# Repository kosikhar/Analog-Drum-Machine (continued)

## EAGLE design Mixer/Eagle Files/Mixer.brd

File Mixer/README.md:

Design Information for Analog Drum Machine Mixer Circuit

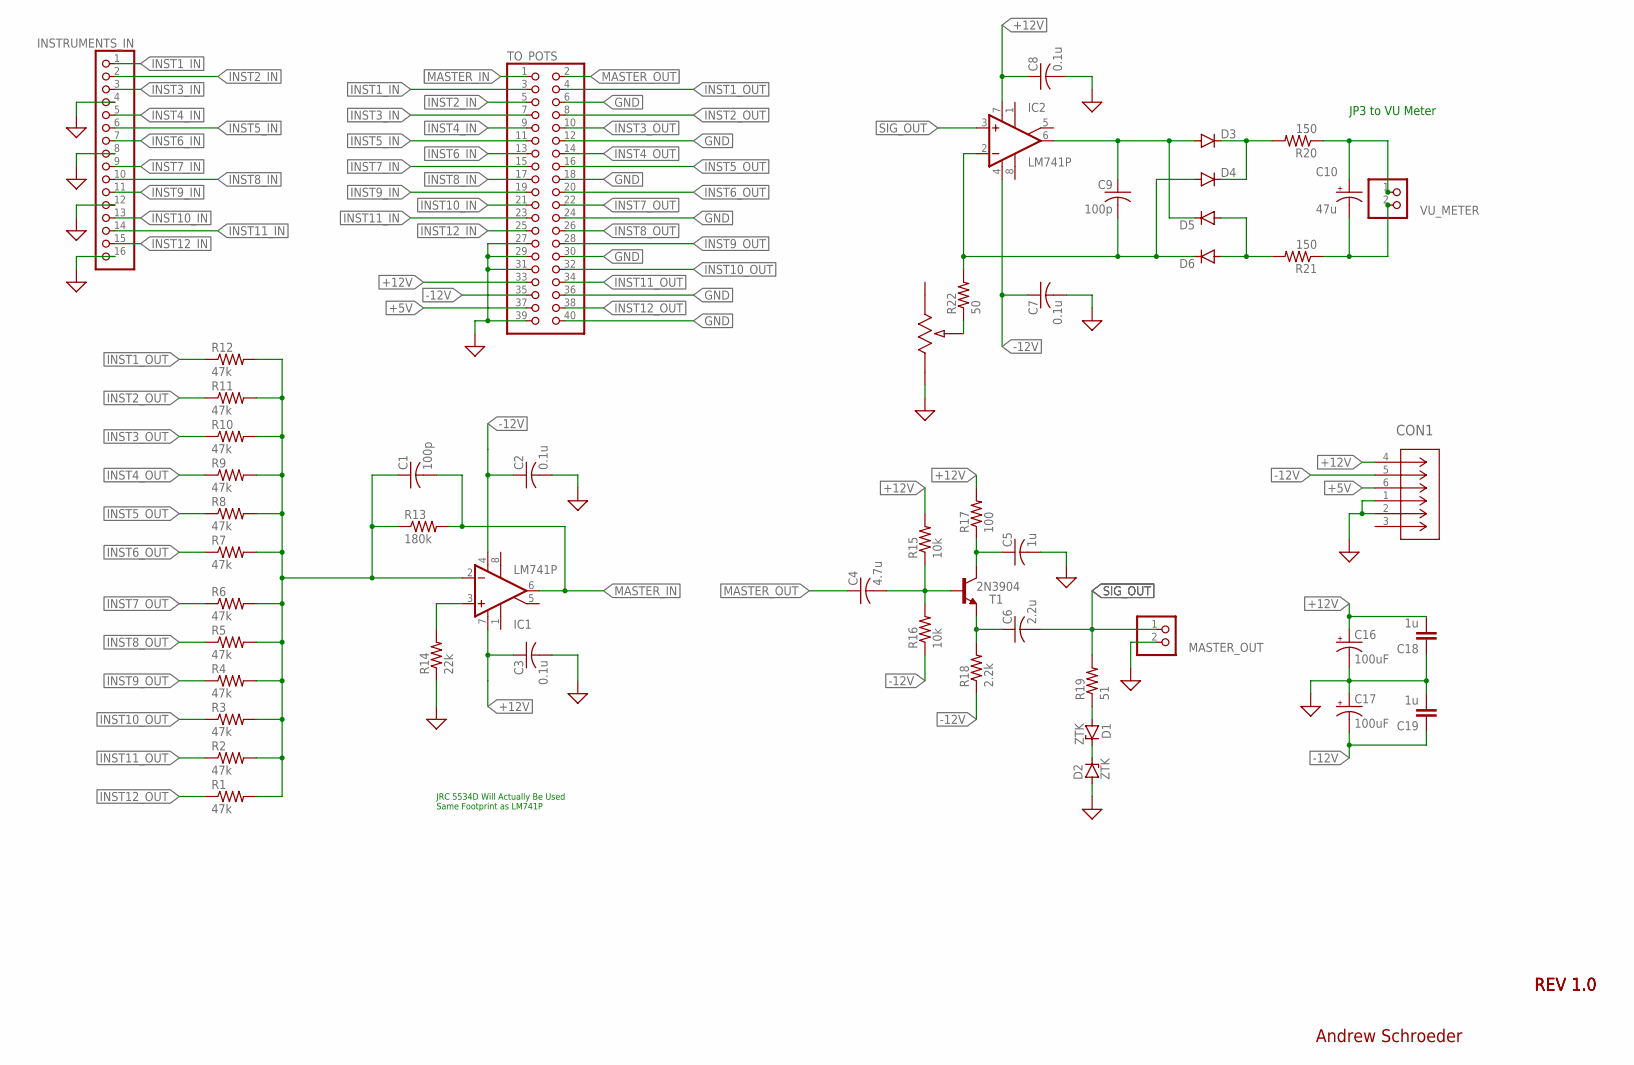
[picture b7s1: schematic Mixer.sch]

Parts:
C1, C9: 100p; C025-025X050
C2, C3, C7, C8: 0.1u; C025-025X050
C4: 4.7u; C025-025X050
C5: 1u; C025-025X050
C6: 2.2u; C025-025X050
C10: 47u; E2-5
C16, C17: 100uF; E5-8,5
C18, C19: 1u; C050-024X044
CON1: 1-770875-01-770875-0_VERTICAL; 1-770875-0
D1, D2: ZTK; DO35Z10
D3, D4, D5, D6: 1N4148DO35-7; DO35-7
IC1, IC2: LM741P; DIL08
INSTRUMENTS_IN: PINHD-1X16; 1X16
MASTER_OUT: PINHD-1X2; 1X02
R1, R2, R3, R4, R5, R6, R7, R8, R9, R10, R11, R12: 47k; 0207/7
R13: 180k; 0207/7
R14: 22k; 0207/7
R15, R16: 10k; 0207/7
R17: 100; 0207/7
R18: 2.2k; 0207/7
R19: 51; 0207/7
R20, R21: 150; 0207/7
R22: 50; 0207/7
R23: PV36W101C01B00; POT_PV36W
T1: 2N3904; TO92
TO_POTS: PINHD-2X20; 2X20
VU_METER: PINHD-1X2; 1X02

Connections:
+5V: CON1.6 (3), TO_POTS.37
+12V: C3.1, C8.1, C16.+, C18.2, CON1.4 (1), IC1.7 (V+), IC2.7 (V+), R15.2, R17.2, TO_POTS.33
-12V: C2.1, C7.1, C17.-, C19.1, CON1.5 (2), IC1.4 (V-), IC2.4 (V-), R16.1, R18.1, TO_POTS.35
GND: C2.2, C3.2, C5.2, C7.2, C8.2, C16.-, C17.+, C18.1, C19.2, CON1.1 (4), CON1.2 (5), D2.A, INSTRUMENTS_IN.4, INSTRUMENTS_IN.8, INSTRUMENTS_IN.12, INSTRUMENTS_IN.16, MASTER_OUT.2, R14.1, R23.3, TO_POTS.6, TO_POTS.12, TO_POTS.18, TO_POTS.24, TO_POTS.27, TO_POTS.29, TO_POTS.30, TO_POTS.31, TO_POTS.36, TO_POTS.39, TO_POTS.40
INST1_IN: INSTRUMENTS_IN.1, TO_POTS.3
INST1_OUT: R12.1, TO_POTS.4
INST2_IN: INSTRUMENTS_IN.2, TO_POTS.5
INST2_OUT: R11.1, TO_POTS.8
INST3_IN: INSTRUMENTS_IN.3, TO_POTS.7
INST3_OUT: R10.1, TO_POTS.10
INST4_IN: INSTRUMENTS_IN.5, TO_POTS.9
INST4_OUT: R9.1, TO_POTS.14
INST5_IN: INSTRUMENTS_IN.6, TO_POTS.11
INST5_OUT: R8.1, TO_POTS.16
INST6_IN: INSTRUMENTS_IN.7, TO_POTS.13
INST6_OUT: R7.1, TO_POTS.20
INST7_IN: INSTRUMENTS_IN.9, TO_POTS.15
INST7_OUT: R6.1, TO_POTS.22
INST8_IN: INSTRUMENTS_IN.10, TO_POTS.17
INST8_OUT: R5.1, TO_POTS.26
INST9_IN: INSTRUMENTS_IN.11, TO_POTS.19
INST9_OUT: R4.1, TO_POTS.28
INST10_IN: INSTRUMENTS_IN.13, TO_POTS.21
INST10_OUT: R3.1, TO_POTS.32
INST11_IN: INSTRUMENTS_IN.14, TO_POTS.23
INST11_OUT: R2.1, TO_POTS.34
INST12_IN: INSTRUMENTS_IN.15, TO_POTS.25
INST12_OUT: R1.1, TO_POTS.38
MASTER_IN: C1.2, IC1.6 (OUT), R13.2, TO_POTS.1
MASTER_OUT: C4.1, TO_POTS.2
unnamed: C9.1, D3.A, D5.C, IC2.6 (OUT)
unnamed: IC1.3 (+IN), R14.2
unnamed: C9.2, D4.A, D6.C, IC2.2 (-IN), R22.2
unnamed: C1.1, IC1.2 (-IN), R1.2, R2.2, R3.2, R4.2, R5.2, R6.2, R7.2, R8.2, R9.2, R10.2, R11.2, R12.2, R13.1
unnamed: D5.A, D6.A, R21.2
unnamed: C4.2, R15.1, R16.2, T1.2 (B)
unnamed: C10.+, R20.1, VU_METER.1
unnamed: C5.1, R17.1, T1.1 (C)
unnamed: D3.C, D4.C, R20.2
unnamed: C6.1, R18.2, T1.3 (E)
unnamed: C10.-, R21.1, VU_METER.2
unnamed: D1.A, R19.1
unnamed: R22.1, R23.2
unnamed: D1.C, D2.C
SIG_OUT: C6.2, IC2.3 (+IN), MASTER_OUT.1, R19.2

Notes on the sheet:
JRC 5534D Will Actually Be Used Same Footprint as LM741P
JP3 to VU Meter
REV 1.0
Andrew Schroeder

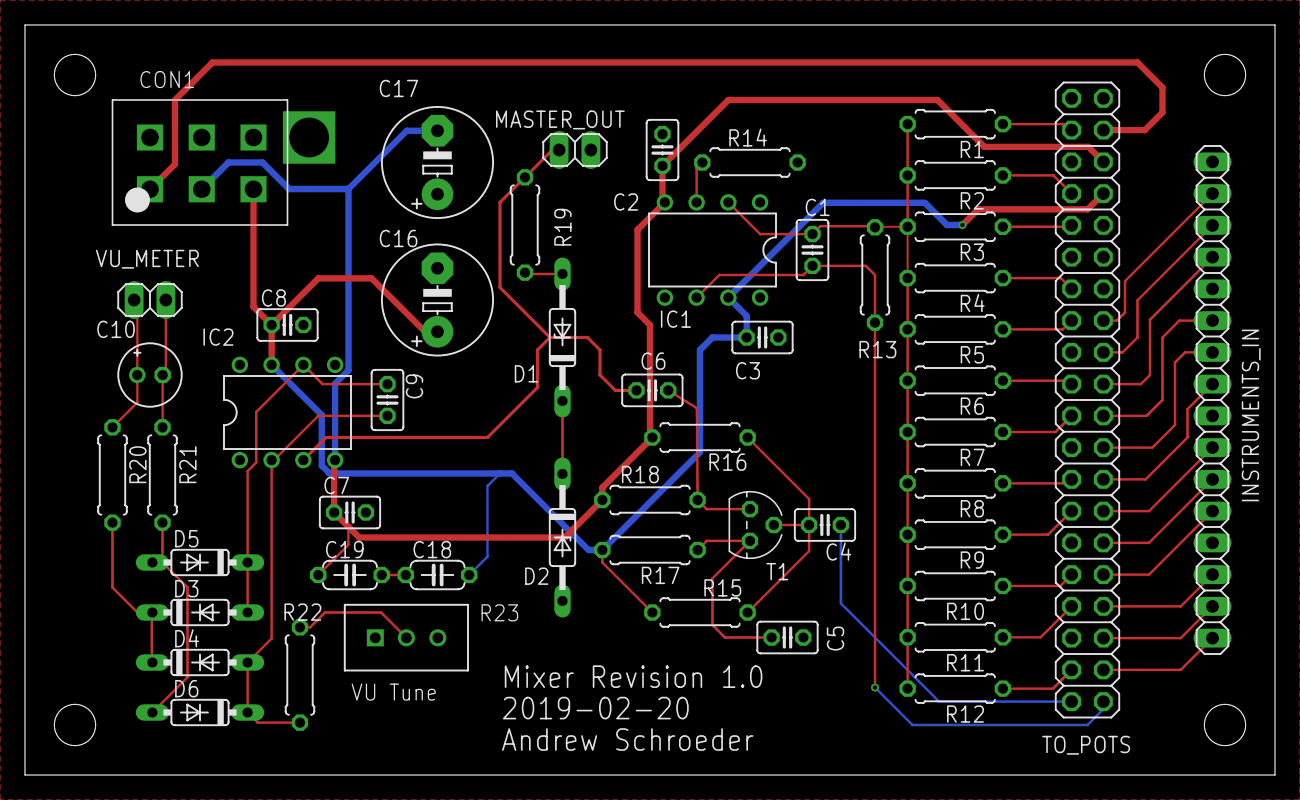
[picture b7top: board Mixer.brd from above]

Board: 2 copper layers, 100.0 x 60.0 mm, 56 parts (0 on the bottom side), 45 nets.

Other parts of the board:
U$1, U$2, U$3, U$4: STAND-OFF
U$5: A5L-LOC

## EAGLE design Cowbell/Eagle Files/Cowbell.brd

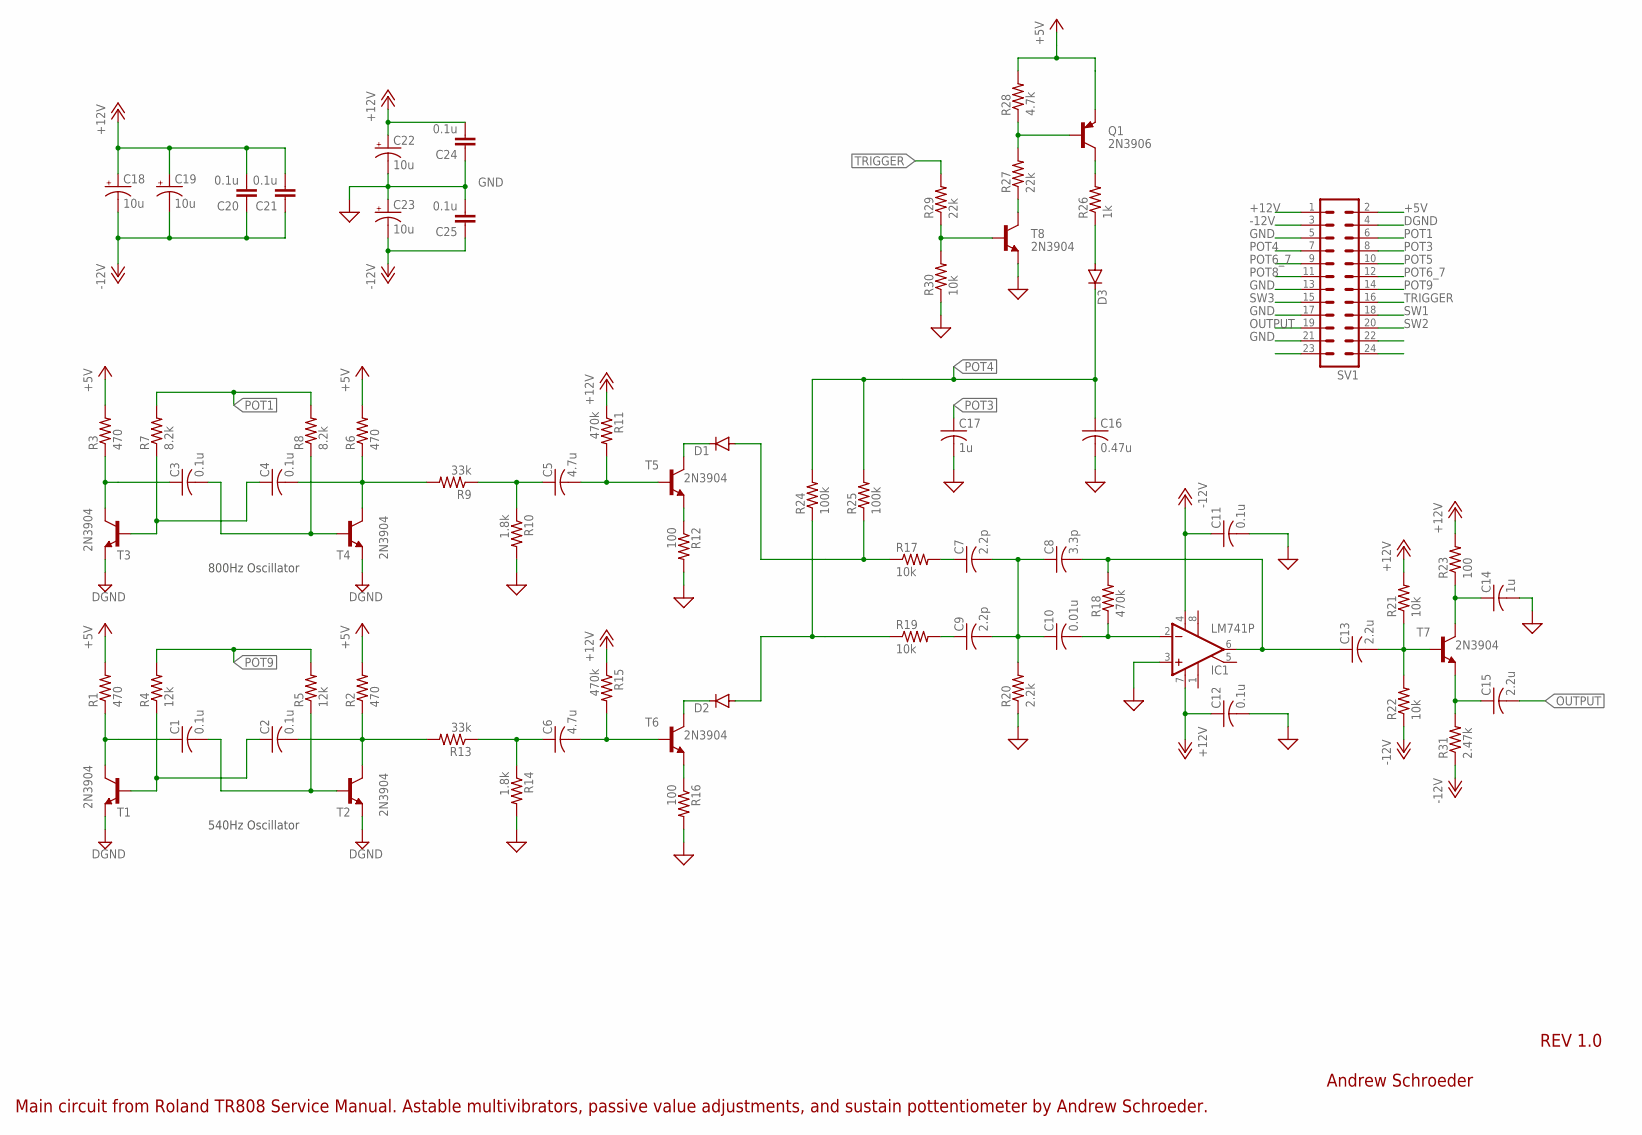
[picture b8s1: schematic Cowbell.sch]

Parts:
C1, C2, C3, C4, C11, C12: 0.1u; C025-024X044
C5, C6: 4.7u; C025-024X044
C7, C9: 2.2p; C025-024X044
C8: 3.3p; C025-024X044
C10: 0.01u; C025-024X044
C13, C15: 2.2u; C025-024X044
C14, C17: 1u; C025-024X044
C16: 0.47u; C025-024X044
C18, C19, C22, C23: 10u; E2,5-6
C20, C21, C24, C25: 0.1u; C050-024X044
D1, D2, D3: 1N4148DO35-7; DO35-7
IC1: LM741P; DIL08
Q1: 2N3906; TO92
R1, R2, R3, R6: 470; 0207/7
R4, R5: 12k; 0207/7
R7, R8: 8.2k; 0207/7
R9, R13: 33k; 0207/7
R10, R14: 1.8k; 0207/7
R11, R15, R18: 470k; 0207/7
R12, R16, R23: 100; 0207/7
R17, R19, R21, R22, R30: 10k; 0207/7
R20: 2.2k; 0207/7
R24, R25: 100k; 0207/7
R26: 1k; 0207/7
R27, R29: 22k; 0207/7
R28: 4.7k; 0207/7
R31: 2.47k; 0207/7
SV1: MA12-2
T1, T2, T3, T4, T5, T6, T7, T8: 2N3904; TO92

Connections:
+5V: Q1.3 (E), R1.2, R2.2, R3.2, R6.2, R28.2, SV1.2
+12V: C12.1, C18.+, C19.+, C20.2, C21.2, C22.+, C24.2, IC1.7 (V+), R11.1, R15.1, R21.2, R23.2, SV1.1
-12V: C11.1, C18.-, C19.-, C20.1, C21.1, C23.-, C25.1, IC1.4 (V-), R22.1, R31.1, SV1.3
DGND: SV1.4, T1.3 (E), T2.3 (E), T3.3 (E), T4.3 (E)
GND: C11.2, C12.2, C14.2, C16.2, C17.2, C22.-, C23.+, C24.1, C25.2, IC1.3 (+IN), R10.2, R12.2, R14.2, R16.2, R20.1, R30.1, SV1.5, SV1.13, SV1.17, SV1.21, T8.3 (E)
unnamed: C4.2, R6.1, R9.2, T4.1 (C)
unnamed: C2.2, R2.1, R13.2, T2.1 (C)
unnamed: C1.1, R1.1, T1.1 (C)
unnamed: C2.1, R4.1, T1.2 (B)
unnamed: C3.1, R3.1, T3.1 (C)
unnamed: C4.1, R7.1, T3.2 (B)
unnamed: C1.2, R5.1, T2.2 (B)
unnamed: C3.2, R8.1, T4.2 (B)
unnamed: C5.1, R9.1, R10.1
unnamed: D1.C, T5.1 (C)
unnamed: C5.2, R11.2, T5.2 (B)
unnamed: R12.1, T5.3 (E)
unnamed: C6.1, R13.1, R14.1
unnamed: C6.2, R15.2, T6.2 (B)
unnamed: R16.1, T6.3 (E)
unnamed: D2.C, T6.1 (C)
unnamed: D1.A, R17.1, R25.1
unnamed: D2.A, R19.1, R24.1
unnamed: C7.1, R17.2
unnamed: C7.2, C8.1, C9.2, C10.1, R20.2
unnamed: C8.2, C13.1, IC1.6 (OUT), R18.2
unnamed: C10.2, IC1.2 (-IN), R18.1
unnamed: C13.2, R21.1, R22.2, T7.2 (B)
unnamed: C9.1, R19.2
unnamed: Q1.1 (C), R26.2
unnamed: C14.1, R23.1, T7.1 (C)
unnamed: C15.1, R31.2, T7.3 (E)
unnamed: R27.1, T8.1 (C)
unnamed: D3.A, R26.1
unnamed: R29.1, R30.2, T8.2 (B)
unnamed: Q1.2 (B), R27.2, R28.1
OUTPUT: C15.2, SV1.19
POT1: R7.2, R8.2, SV1.6
POT3: C17.1, SV1.8
POT4: C16.1, D3.C, R24.2, R25.2, SV1.7
POT5: SV1.10
POT6_7: SV1.9, SV1.12
POT8: SV1.11
POT9: R4.2, R5.2, SV1.14
SW1: SV1.18
SW2: SV1.20
SW3: SV1.15
TRIGGER: R29.2, SV1.16

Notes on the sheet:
540Hz Oscillator
800Hz Oscillator
Andrew Schroeder
REV 1.0
Main circuit from Roland TR808 Service Manual. Astable multivibrators, passive value adjustments, and sustain pottentiometer by Andrew Schroeder.

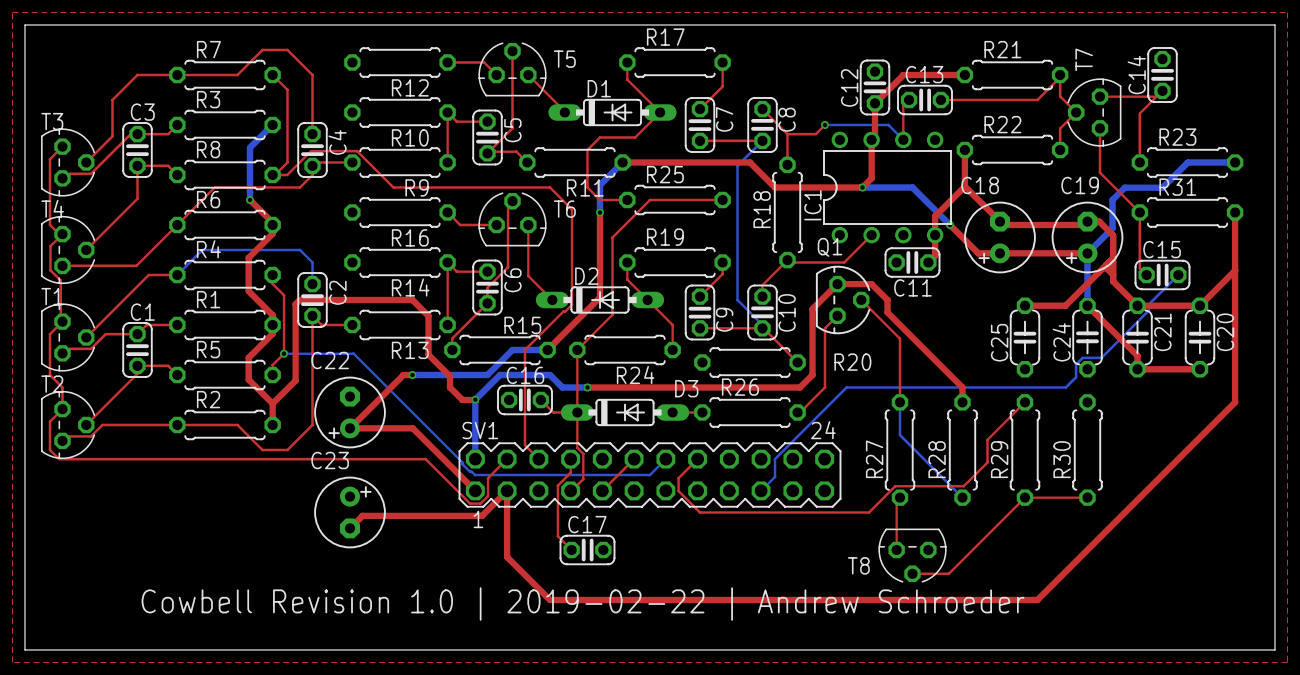
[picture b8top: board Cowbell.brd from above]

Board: 2 copper layers, 100.0 x 50.0 mm, 71 parts (0 on the bottom side), 43 nets.

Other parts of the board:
U$6: A5L-LOC

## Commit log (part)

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2018-10-19 Added kick drum and updated gitignore
2018-10-20 preliminary
2018-11-07 Create Main board
2018-11-07 removed empty file
2018-11-07 First push
    Initial upload.
2018-11-07 Schematic
    Only schematic added
2018-11-11 some changes to the kick
2018-11-12 Created new branch and README.md for Mixer
2018-11-12 Created Input Module Simulation-Still Under Testing
2018-11-12 Added Mixer Input Module
2018-11-13 Added power supply V2
2018-11-13 Added Summing Circuit
2018-11-13 Deleted Temporary Files
2018-11-14 Added Hi Hat simulation
2018-11-14 Added Amplifier Stage and Selected Caps for Cutoff Frequency=40kHz
2018-11-14 CIrcuit for switches
    Seperate schematic for switches (Updated)
2018-11-14 Cleaned up schematics
    Instruments, switches and initial diagram.
2018-11-14 Updated schematics
    Removed #s files
2018-11-16 Added BOM
2018-11-16 missed some parts for the BOM
2018-11-18 Kick drum (#1)
    * some changes to the kick
    * Added BOM
    * missed some parts for the BOM
2018-11-19 Initial circuits
    Similations seem okay.
2018-11-20 Added Subcircuit model for LM741
2018-11-20 Added Cowbell Simulation Files
2018-11-22 changes to envolope
2018-11-22 changes to feedback/osc
2018-11-25 This is pretty much close to the final form
    Not much needed to change here. Kick sounds great
2018-11-25 changes to some names and added sounds
2018-11-25 added block diagram
2018-11-26 Created Enclosure Branch and uploaded models for backup
2018-11-26 added monochrome pdf print out
2018-11-26 Changed block diagram
2018-11-26 Sequencer State Diagrams update
2018-11-26 Work on state diagram
2018-11-26 update State diagram
2018-11-26 updated state diagram
2018-11-26 Added to State Diagram
2018-11-26 Updated sequencer diagram
2018-11-26 finishing touches
2018-11-26 K I think this is done
2018-11-26 k this should be good now
2018-11-26 Committing to switch branches
2018-11-26 changed name of BOM
2018-11-26 Added BOM list
2018-11-27 Updated Power Supply Branch
    Updated Power supply branch with newest LTspice models, as well as Eagle Schematic and block diagram. BOM updated as well.
2018-11-27 Updated Hi Hat
    Updated Hi Hat simulation and added BOM and block diagram
2018-11-29 Updated LTspice and wave files
    Added the LTspice simulation that uses the white noise wave file. Uploaded new sounds
2018-12-08 Added version with diff amp
2018-12-09 Added the Schmitt Triggers
2018-12-09 moved blocks over
2018-12-09 revert
2018-12-09 initialize
2018-12-10 added full diagram
2018-12-18 intialized more files
2018-12-19 Added more intializers
2018-12-20 Added a dedicated timer class, worked on shiftregister class
2018-12-21 Got the timer interrupt working.
2018-12-21 work on timers/interrupt/SIPO
2018-12-22 This doesn't work. Need to fix
2018-12-24 okay it seems I got stuff to work now
2018-12-24 can sucessfully write to a seven segment
2018-12-25 code tested with a second SIPO shift register
2018-12-25 Made timer faster. Small cleanup
2018-12-26 Code cleanup and optimization
    - Added in a primitive task mangement system
    - Optimized the speed of shifts.
2019-01-14 added 1ms pulse source
2019-01-20 Organized folder structure.
2019-01-21 Made changes to power supply PCB
2019-01-24 started eagle schematic
2019-01-24 work on schematic
2019-01-26 Power supply PCB still in progress
2019-01-26 perf board for instruments plus gerbers
2019-01-26 perf board for instruments plus gerbers (#2)
2019-01-26 Finished PCB
2019-01-27 Pretty much done schematic
2019-01-28 Just Viewed
2019-01-28 Updated Mixer
2019-01-28 Just switching branches
2019-01-28 Switching Branches Again
2019-01-28 Revised Mixer
2019-01-28 Added Mixer_BOM
2019-01-28 updated BOM
2019-01-28 Power supply (#3)
    * preliminary
    * Added power supply V2
    * Update Power Supply/Thumbs.db
    * Updated Power Supply Branch
    Updated Power supply branch with newest LTspice models, as well as Eagle Schematic and block diagram. BOM updated as well.
    * Added version with diff amp
2019-01-28 Switching Branches
2019-01-29 work on pcb.
    -laying out components
2019-01-30 Wiring PCB
    -Almost done!
2019-01-30 Updated some capacitors
    Changed some caps from 2.2uF to 4.7uF, got rid of a 4.7uF
2019-01-30 Added Revised Order Form
2019-01-31 I think im done
2019-01-31 Analog Drum (#4)
    * some changes to the kick
    * Added BOM
    * missed some parts for the BOM
    * changes to envolope
    * changes to feedback/osc
    * This is pretty much close to the final form
2019-01-31 Made Updates
    Made Updates
2019-02-03 Create VU meter schematic.sch
    VU meter initial commit
2019-02-03 Update VU meter schematic.sch
    Fixed some routing issues.
2019-02-03 PCB files
    Updated with PCB files
2019-02-04 Major overhaul of task managment.
    - Not tested yet, but it compiles
2019-02-04 small changes
2019-02-04 u don ducked
2019-02-05 New backend complete and works
    -Should be easier to read and find out what things do
    -Should be easier to add new functionality
2019-02-05 Added folders clean up mess of files
2019-02-07 This probs dont work
2019-02-08 Added shift register piso
2019-02-08 not complete
    -working on removing bugs
2019-02-08 fixed bug.
2019-02-09 Added some class definitions
2019-02-09 added some headers to project
2019-02-10 added some declarations
2019-02-12 Minor modifications
2019-02-15 Create Main board.sch
    Version 1
2019-02-17 Removed op-amp buffer stage from mixer circuit.
2019-02-17 Nothing important
2019-02-18 Added circuitry for testing frequency response.
2019-02-18 Cleaned up useless files.
2019-02-20 Built preliminary Mixer Schematic
2019-02-20 Update Main board.sch
    Updated pinouts. Need feedback.
2019-02-21 Created Board File
2019-02-21 Completed Mixer Board Layout
2019-02-21 Organized files and folders.
2019-02-21 Added to input polling task
2019-02-21 Create Main board.brd
    Initial version. Could definitely be improved.
2019-02-21 Update Main board.sch
    Updated version with wiring.
2019-02-21 Update Main board.brd
    Version 2
2019-02-22 Updated LTspice file with values used during prototype on breadboard.
2019-02-22 Addeed design references folder.
2019-02-22 Touched up schematic and started board layout.
2019-02-22 Placed parts on .brd file. Have to route yet.
2019-02-22 Repositioned main header.
2019-02-22 Completed board layout, generated CAM files, and organized files and folders.
2019-02-22 Ran DRC and fixed errors. Generated CAM files and updated images.
2019-02-22 button input
2019-02-22 Added note to clarify analog and digital ground
    Added note to clarify analog and digital ground. Pin 3 is digital, 1 & 2 are analog.
2019-02-22 Made some small changes for design review. More yet to be made.
2019-02-23 Got analog input to work
2019-02-23 Updated Solidworks model with accurate dimensions.
2019-02-23 Made the trigger fall in line with BPM
2019-02-24 Made BPM display update faster
2019-02-25 Started Snare PCB
2019-03-03 updated input code
2019-03-03 exported library
2019-03-03 Edited TE6Pin
2019-03-03 Updated TE part
2019-03-03 Added 6Pin TE vertical
2019-03-03 ignoring local backups
2019-03-03 Main board
    Relabelled everything with power supply, labelled and redid traces.
2019-03-03 Finished Schematic
    Finished Schematic
2019-03-04 Updated Snare schematic
    updated snare schematic
2019-03-04 Started PCB
    Started working on the PCB
2019-03-04 First draft of schematic
2019-03-04 Finished PCB
    Finished the snare PCB
2019-03-04 Implemented changes from design review meeting.
2019-03-04 fixed TE pinout
2019-03-05 Sequencer microcontroller (#7)
    * Sequencer State Diagrams update
    * Work on state diagram
    * update State diagram
    * updated state diagram
    * Added to State Diagram
    * Updated sequencer diagram
2019-03-05 Version 2 of mainboard
    Corrected lots of thingamajics.
2019-03-05 Finished Silkscreen
2019-03-05 Added a few missing components
    Added a few missing components. 3 coupling capacitors were missing
2019-03-05 Generated Gerbers
2019-03-05 Created Gerbers again and fixed Seeed DRC errors
    Created Gerbers again and fixed Seeed DRC errors
2019-03-05 Created to interface panel.
2019-03-05 Finished layout - needs silk screen
2019-03-05 some track adjustments
2019-03-05 Version 3 of mainboard
    Added sequencer pinouts and manually did all traces.
2019-03-05 Version 4
    Added ground traces to previous version.
2019-03-05 This board should work
2019-03-05 Swapped Instruments 2 and 3
    Swapped instruments 2 and 3 so they are in proper order
2019-03-06 Added silk screen
2019-03-06 PATA breakout
2019-03-06 did DRC
2019-03-06 Just added some SR
2019-03-06 Added 100ohm resistor
2019-03-06 updated gitignore
2019-03-06 Attached traces to resistor and created gerbers
2019-03-06 Fixed air wires and created gerbers
2019-03-06 some board layout
2019-03-07 breakout backside
2019-03-07 Finished routing
2019-03-07 Finished top board - ran DRC
2019-03-07 Pata breakout sequencer (#10)
    * Just added some SR
    * Update .gitignore
    * Delete Analog Drum_2019-01-31.zip
    * updated gitignore
    * some board layout
    * split board into 2
2019-03-07 Main board (#8)
    * First push
    Initial upload.
    * Schematic
    Only schematic added
    * Delete Main board schematic.zip
    * CIrcuit for switches
2019-03-07 Pata breakout (#9)
    * PATA breakout
    * did DRC
    * Delete .PATA Breakout.sch.lck
2019-03-07 Cowbell (#6)
    * preliminary
    * Added power supply V2
    * Update Power Supply/Thumbs.db
    * Added Cowbell Simulation Files
    * Committing to switch branches
    * Added the Schmitt Triggers
2019-03-07 Mixer (#5)
    * Created new branch and README.md for Mixer
    * Created Input Module Simulation-Still Under Testing
    * Added Mixer Input Module
    * Added Summing Circuit
    * Deleted Temporary Files
    * Added Amplifier Stage and Selected Caps for Cutoff Frequency=40kHz
2019-03-07 cleanup
2019-03-07 Snare (#11)
    * Started Snare PCB
    * Finished Schematic
    Finished Schematic
    * Updated Snare schematic
    updated snare schematic
    * Started PCB
2019-03-07 Changed hole sizes for rotary encoders on measure select and bpm controls.
2019-03-07 Created DWG and DXF files for the top panel for machine shop.
2019-03-07 Updated top panel pdf with new dimensions.
2019-03-11 Started Hi-Hat PCB
    Started Hi-Hat PCB
2019-03-11 Completed most of hi-hat schematic
2019-03-11 added rotary switch classs
2019-03-12 Changed resistors out for shorter ones
    changed resistors out for shorter ones
2019-03-13 Made a few adjustments on top panel, made back panel.
2019-03-13 Updated back panel drawing.
2019-03-14 Added piano hinge holes, screw holes, and swapped two holes for Koltin.
2019-03-15 Did work on rotary encoder class
2019-03-16 Added a bunch of task objects
2019-03-16 Changes to output printing behaviour
    -still bugs
2019-03-16 Updates to cymbals
2019-03-17 Lots of changes, still lots of classes to build
2019-03-18 continuing to build new components
2019-03-18 project save
2019-03-19 Worked on hi-hat
2019-03-20 Made more progress on hi-hat
2019-03-20 worked more on laying out PCB
2019-03-21 Worked on Hi-hat and waveform generator board
    Changed trimpots to the proper part. Added test points to the waveform generator board and fixed silkscreen, ran DRC.
2019-03-22 Worked more on cymbals
2019-03-23 did something
2019-03-26 removed some things we dont need
2019-03-26 Still much to do just pushing changes.
2019-03-26 forgot to save project in last push
2019-03-28 More major object building
    - Issue with compiling "RotarySwitch"
2019-03-29 Got it all to compile
    still some building required.
2019-03-29 removed unnessary declaration
2019-03-31 Added text
2019-03-31 worked on intrumenttrigger object
2019-04-01 got trigger working
2019-04-04 Updates from last testing
2019-04-09 added check task
2019-04-10 defined all shiftregisters
2019-04-10 added trigger declaration
2019-04-10 modified defines
2019-04-10 added trigger stuff and more
2019-04-10 update thangs
2019-04-11 Cleaned up schematics
2019-04-12 stuff used for presentation
2019-04-25 Updated cymbal schematics
2019-04-25 updated schematic
2019-04-26 Made a change to the schematic
